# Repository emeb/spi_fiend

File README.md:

# spi_fiend
STM32F042-based USB to SPI device for programming iCE40 FPGAs

Most open-source projects that use Lattice iCE40 FPGAs rely on the FTDI
FT2232 High-speed UART/FIFO chip to provide a SPI interface for programming
the FPGA and SPI Flash chip which contains the bitstream for self-configuration
at power-up. I've got nothing against FTDI, but the chips are big, require
a crystal and are fairly expensive in DIY quantities. On top of that I've been
using STM32 for years and have been looking for an excuse to dig into some
more USB applications so a USB to SPI bridge seemed like a good place to start.

This device uses the small and inexpensive STM32F042F6P6 in a 20-pin TSSOP
package. It supports crystal-less USB operation by syncing its internal RC
oscillator to the USB SOF signal and has enough SRAM and Flash to support a
moderately complex feature set:

* USB powered
* Crystal-less operation
* Presents an ordinary ACM / CDC class device that looks like a serial port.
* Supports direct loading into the iCE40 SRAM for quick development cycles.
* Supports read/write/erase of standard SPI Flash devices used for FPGA configuration.
* Includes automatic swapping of MOSI/MISO when switching between FPGA and SPI Flash.
* MCU Serial port is pinned out for debugging and future expansion.

## prerequisites
To build this you will need the following tools:

* Kicad - schematic & PCB editor.
* GCC ARM Embedded - cross-compiler for ARM Cortex M: https://developer.arm.com/tools-and-software/open-source-software/developer-tools/gnu-toolchain/gnu-rm
* dfu-util - USB DFU driver application available in most distributions.
* Basic Linux user C compiler (for host application)

## Building Hardware

The board design is available in the 'hardware' directory. The Kicad PCB can
be submitted directly to OSHpark.com, or traditional Gerbers can be exported
using the application. Part values and packages are noted in the schematic.

Note: in the Revision 1 PCB layout the USB connector doesn't overhang the PCB
edge and there is a slight interference with the lower lip. Filing a slight
chamfer on the PCB edge under the connector will allow it to sit flush to the
board.

## Building Firmware

The [Firmware README](firmware/README.md) has instructions on building the
preferred firmware for the SPI Fiend.

## Building Host Application

The host appliction runs on a Linux PC and communicates with the hardware
device via standard USB Serial protocols. Build the host application by changing
to the 'host' directory and executing 'make'. The built-in help should provide
a guide to available options, but here's a quick list of common actions:

* load a binary into the FPGA: ./cdc_prog BINARY_FILE
* load a binary into SPI Flash: ./cdc_prog -a ADDRESS -w BINARY_FILE
* read SPI flash contents to a file: ./cdc_prog -a ADDRESS -l LENGTH -r > OUTPUT_FILE
* erase SPI FLASH block: ./cdc_prog -a ADDRESS -e
* read SPI Flash ID: ./cdc_prog -i

In ordinary operation, the LED nearest the USB connector lights to indicate powerup,
the center LED lights when an error is detected during operation and the outer LED
lights when programming SPI flash.

## Status
### 2019-05-06
Initial commit with hardware, firmware and host application

### 2022-11-11
Updated with dual firmware that supports FPGA, flash and UART

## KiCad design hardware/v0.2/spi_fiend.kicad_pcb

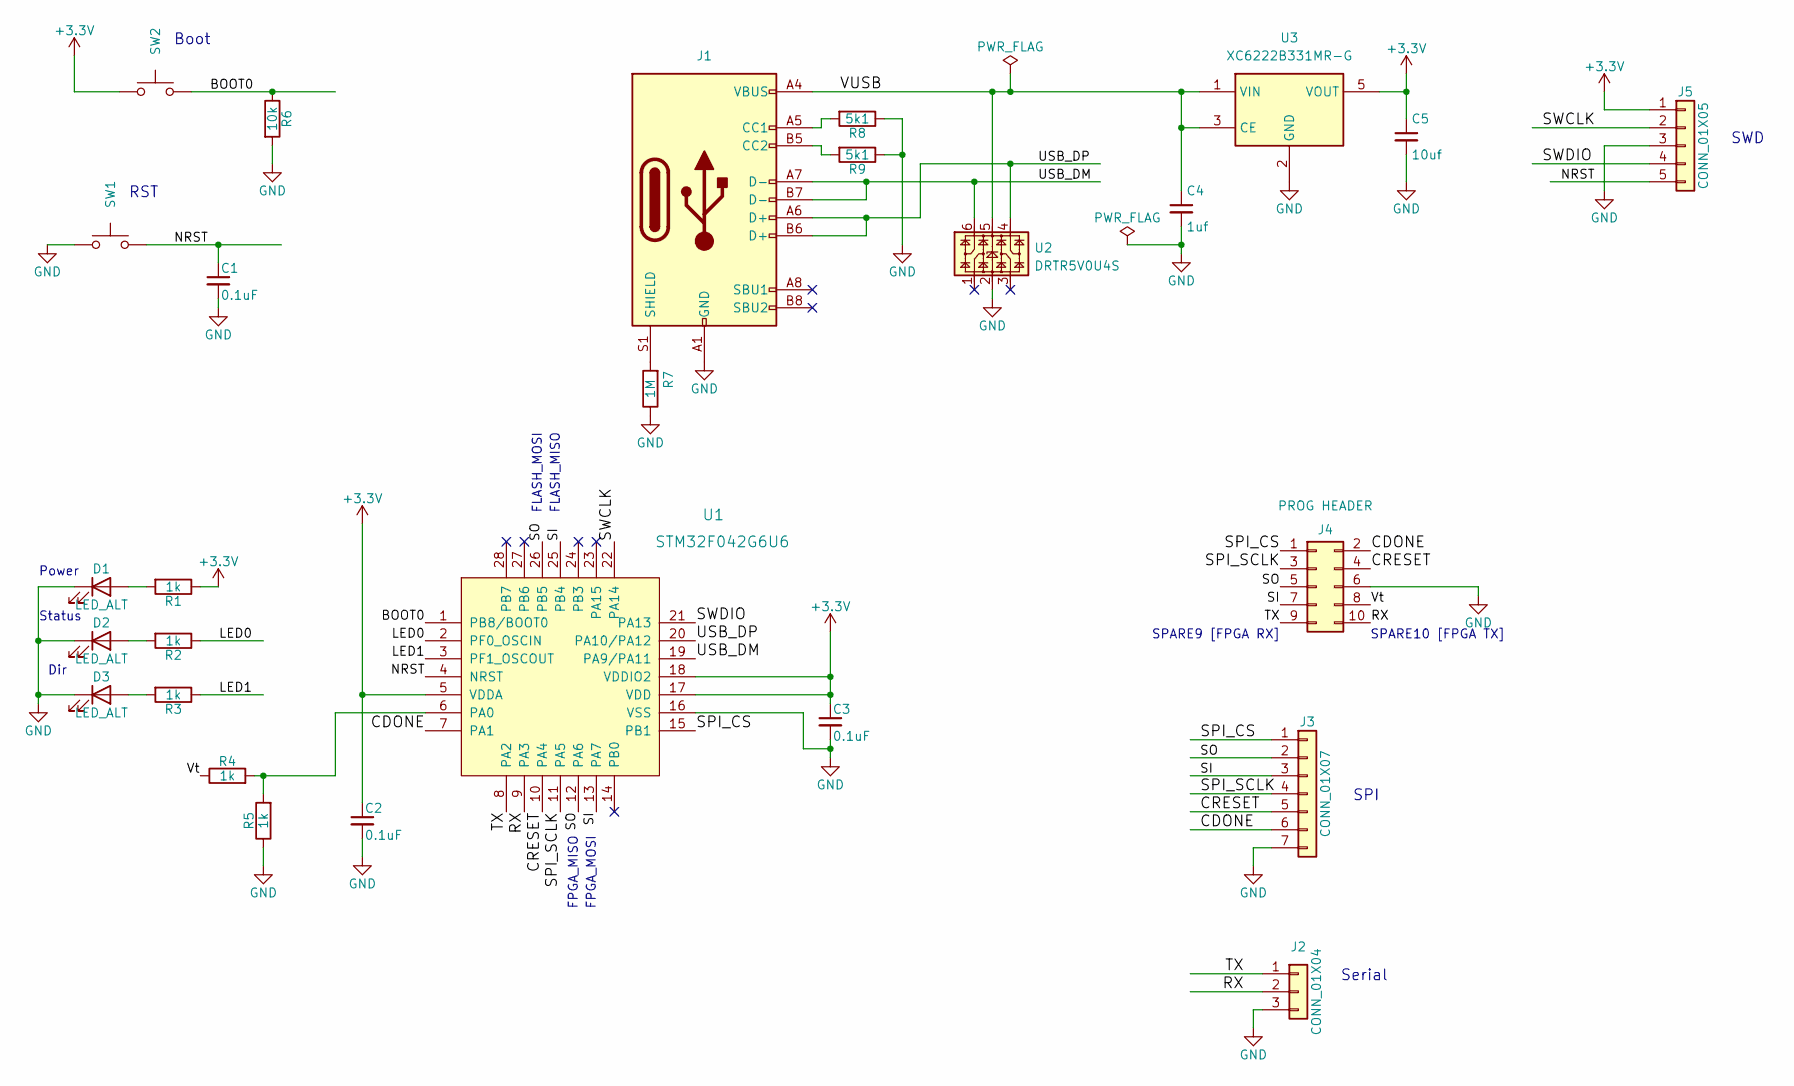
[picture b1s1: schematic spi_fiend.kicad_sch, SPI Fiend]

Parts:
C1, C2, C3: 0.1uF; C_0402_1005Metric
C4: 1uf; C_0402_1005Metric
C5: 10uf; C_0805_2012Metric
D1, D2, D3: LED_ALT; LED_0603_1608Metric
J1: USB_C_Receptacle_USB2.0; USB_C_Receptacle_HRO_TYPE-C-31-M-12
J2: CONN_01X04; PinHeader_1x03_P2.54mm_Vertical
J3: CONN_01X07; PinHeader_1x07_P2.54mm_Vertical
J4: PROG HEADER; PinHeader_2x05_P1.27mm_Vertical_SMD
J5: CONN_01X05; PinHeader_1x05_P2.54mm_Vertical
R1, R2, R3, R4, R5: 1k; R_0402_1005Metric
R6: 10k; R_0402_1005Metric
R7: 1M; R_0402_1005Metric
R8, R9: 5k1; R_0402_1005Metric
SW1, SW2: SW_Push; SW_SPST_PTS815
U1: STM32F042G6U6; IC_STM32F042G6U6
U2: DRTR5V0U4S; SOT-363_SC-70-6
U3: XC6222B331MR-G; SOT-23-5

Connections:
+3.3V: C2.1, C3.1, C5.1, J5.1, R1.1, SW2.1, U1.5 (VDDA), U1.17 (VDD), U1.18 (VDDIO2), U3.5 (VOUT)
/BOOT0: R6.1, SW2.2, U1.1 (PB8/BOOT0)
/CDONE: J3.6, J4.2, U1.7 (PA1)
/CRESET: J3.5, J4.4, U1.10 (PA4)
/LED0: R2.1, U1.2 (PF0_OSCIN)
/LED1: R3.1, U1.3 (PF1_OSCOUT)
/NRST: C1.1, J5.5, SW1.2, U1.4 (NRST)
/RX: J2.2, J4.10, U1.9 (PA3)
/SI: J3.3, J4.7, U1.13 (PA7), U1.25 (PB4)
/SO: J3.2, J4.5, U1.12 (PA6), U1.26 (PB5)
/SPI_CS: J3.1, J4.1, U1.15 (PB1)
/SPI_SCLK: J3.4, J4.3, U1.11 (PA5)
/SWCLK: J5.2, U1.22 (PA14)
/SWDIO: J5.4, U1.21 (PA13)
/TX: J2.1, J4.9, U1.8 (PA2)
/USB_DM: J1.A7 (D-), J1.B7 (D-), U1.19 (PA9/PA11), U2.6
/USB_DP: J1.A6 (D+), J1.B6 (D+), U1.20 (PA10/PA12), U2.4
/VUSB: C4.1, J1.A4 (VBUS), J1.A9 (VBUS), J1.B4 (VBUS), J1.B9 (VBUS), U2.5, U3.1 (VIN), U3.3 (CE)
/Vt: J4.8, R4.1
GND: C1.2, C2.2, C3.2, C4.2, C5.2, D1.1 (K), D2.1 (K), D3.1 (K), J1.A1 (GND), J1.A12 (GND), J1.B1 (GND), J1.B12 (GND), J2.3, J3.7, J4.6, J5.3, R5.1, R6.2, R7.1, R8.1, R9.1, SW1.1, U1.16 (VSS), U2.2, U3.2 (GND)
unnamed: D1.2 (A), R1.2
unnamed: D2.2 (A), R2.2
unnamed: D3.2 (A), R3.2
unnamed: J1.A5 (CC1), R8.2
unnamed: J1.B5 (CC2), R9.2
unnamed: J1.S1 (SHIELD), R7.2
unnamed: R4.2, R5.2, U1.6 (PA0)

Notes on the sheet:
FPGA_MISO
SWD
FPGA_MOSI
Serial
RST
Status
SPI
Power
Dir
FLASH_MOSI
Boot
SPARE9 [FPGA RX]
FLASH_MISO
SPARE10 [FPGA TX]

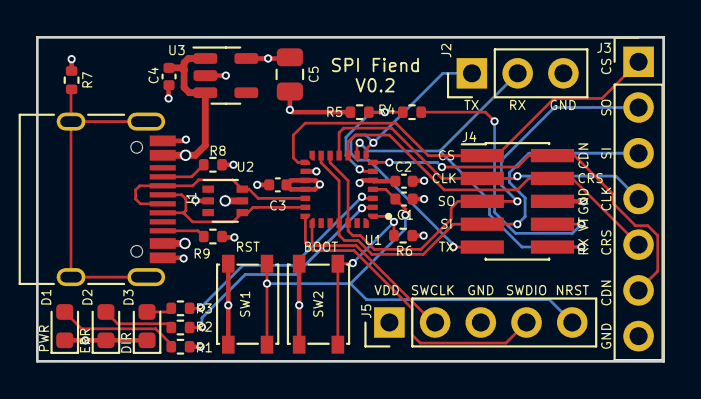
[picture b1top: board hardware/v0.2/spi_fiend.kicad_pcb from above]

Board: 4 copper layers, 34.8 x 18.0 mm, 28 parts (1 on the bottom side), 27 nets.

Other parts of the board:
Ref**: Val**; avatar_small

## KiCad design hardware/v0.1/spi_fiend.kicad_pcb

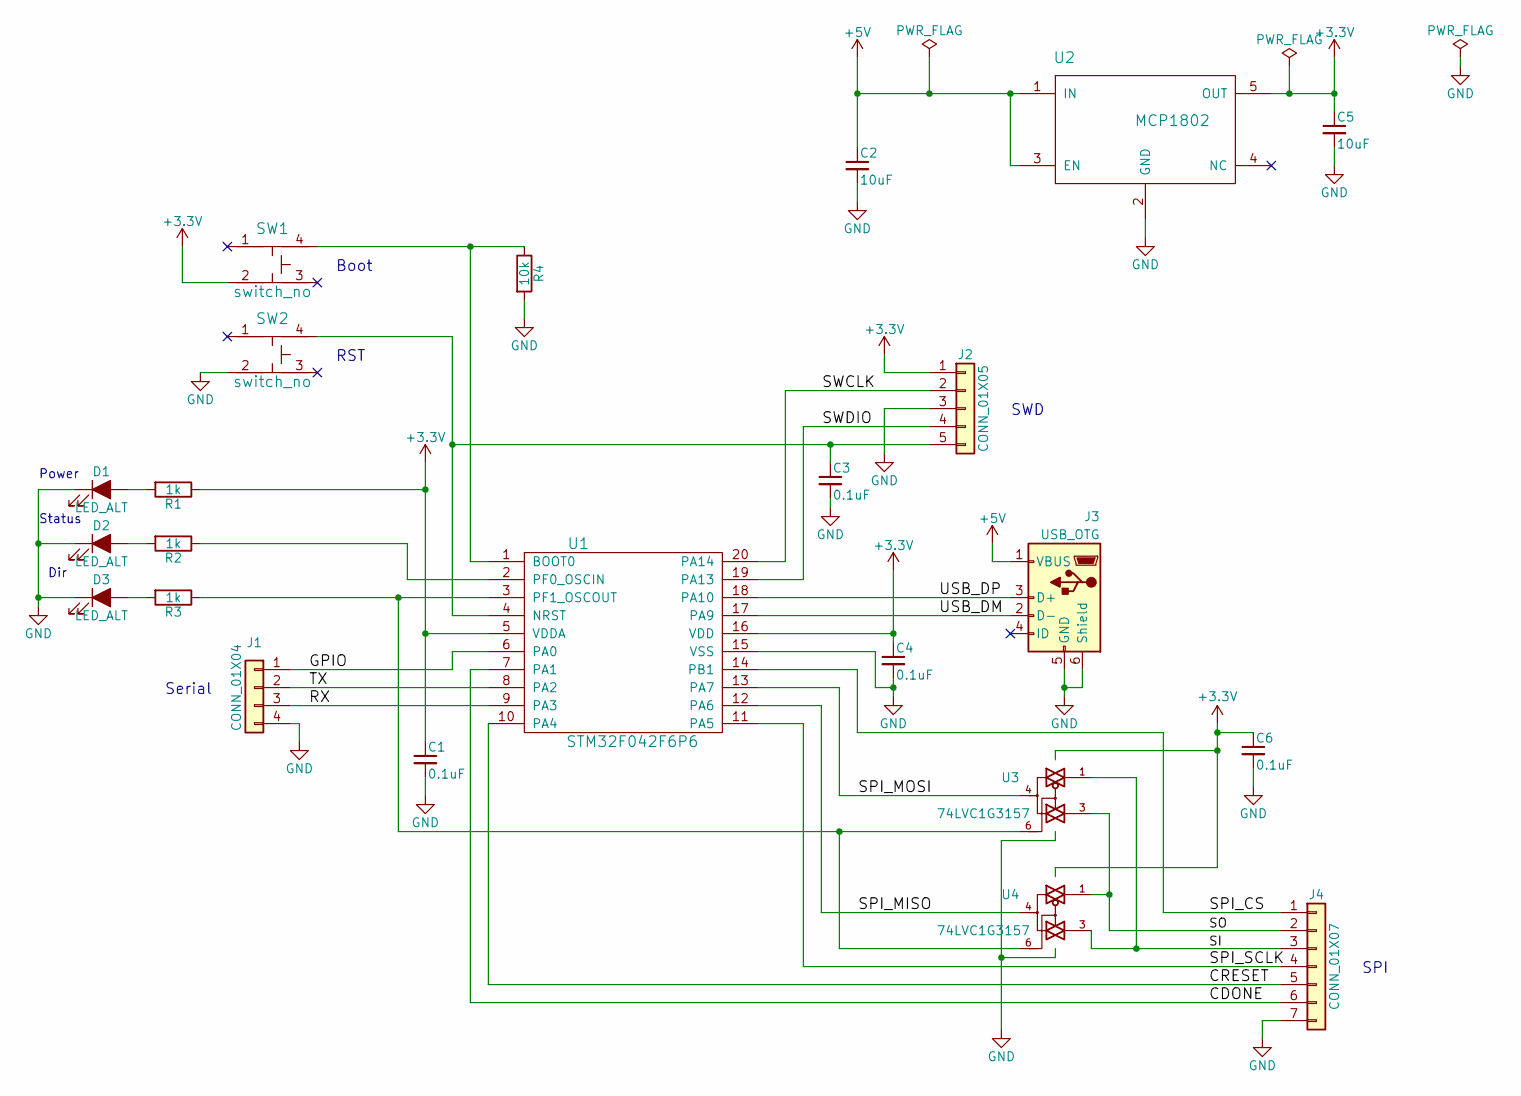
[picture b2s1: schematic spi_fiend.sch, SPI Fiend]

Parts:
C1, C3, C4, C6: 0.1uF; C_0603_HandSoldering
C2, C5: 10uF; C_0805_HandSoldering
D1, D2, D3: LED_ALT; LED_0603_HandSoldering
J1: CONN_01X04; Pin_Header_Straight_1x04_Pitch2.54mm
J2: CONN_01X05; Pin_Header_Straight_1x05_Pitch2.54mm
J3: USB_OTG; USB_Micro-B_10103594-0001LF_NoSlot
J4: CONN_01X07; Pin_Header_Straight_1x07_Pitch2.54mm
R1, R2, R3: 1k; R_0603_HandSoldering
R4: 10k; R_0603_HandSoldering
SW1, SW2: switch_no; PUSHBUTTON_SMD_KMR2
U1: STM32F042F6P6; TSSOP-20_4.4x6.5mm_Pitch0.65mm
U2: MCP1802; SOT-23-5_HandSoldering
U3, U4: 74LVC1G3157; SOT-363_SC-70-6_Handsoldering

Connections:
+3V3: C1.1, C4.1, C5.1, C6.1, J2.1, R1.1, SW1.2, U1.5 (VDDA), U1.16 (VDD), U2.5 (OUT), U3.5 (VCC), U4.5 (VCC)
+5V: C2.1, J3.1 (VBUS), U2.1 (IN), U2.3 (EN)
/CDONE: J4.6, U1.7 (PA1)
/CRESET: J4.5, U1.10 (PA4)
/GPIO: J1.1, U1.6 (PA0)
/RX: J1.3, U1.9 (PA3)
/SI: J4.3, U3.1, U4.3
/SO: J4.2, U3.3, U4.1
/SPI_CS: J4.1, U1.14 (PB1)
/SPI_MISO: U1.12 (PA6), U4.4
/SPI_MOSI: U1.13 (PA7), U3.4
/SPI_SCLK: J4.4, U1.11 (PA5)
/SWCLK: J2.2, U1.20 (PA14)
/SWDIO: J2.4, U1.19 (PA13)
/TX: J1.2, U1.8 (PA2)
/USB_DM: J3.2 (D-), U1.17 (PA9)
/USB_DP: J3.3 (D+), U1.18 (PA10)
GND: C1.2, C2.2, C3.2, C4.2, C5.2, C6.2, D1.1 (K), D2.1 (K), D3.1 (K), J1.4, J2.3, J3.5 (GND), J3.6 (Shield), J4.7, R4.2, SW2.2, U1.15 (VSS), U2.2 (GND), U3.2 (GND), U4.2 (GND)
unnamed: C3.1, J2.5, SW2.4, U1.4 (NRST)
unnamed: D1.2 (A), R1.2
unnamed: D2.2 (A), R2.2
unnamed: D3.2 (A), R3.2
unnamed: R2.1, U1.2 (PF0_OSCIN)
unnamed: R3.1, U1.3 (PF1_OSCOUT), U3.6, U4.6
unnamed: R4.1, SW1.4, U1.1 (BOOT0)

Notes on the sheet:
Boot
RST
Serial
SPI
SWD
Power
Status
Dir

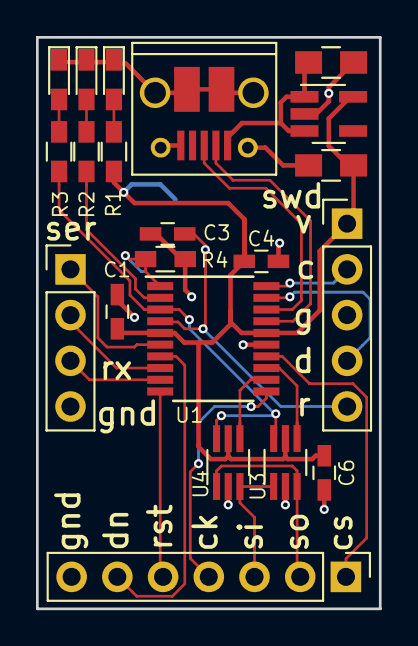
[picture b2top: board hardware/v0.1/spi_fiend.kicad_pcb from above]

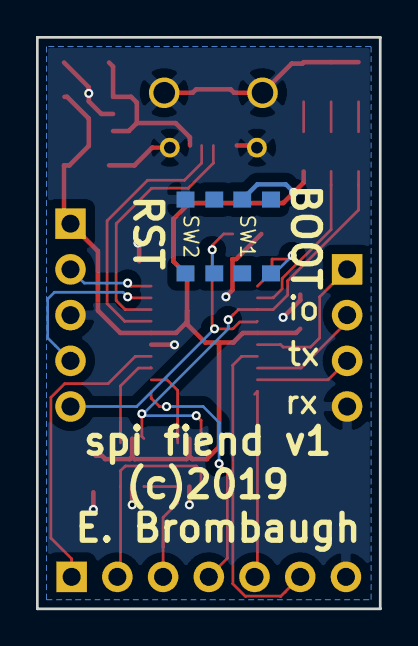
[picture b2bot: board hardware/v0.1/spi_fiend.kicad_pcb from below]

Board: 2 copper layers, 19.1 x 31.8 mm, 23 parts (2 on the bottom side), 25 nets.

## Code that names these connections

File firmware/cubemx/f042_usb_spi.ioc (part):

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Mcu.Name=STM32F042F6Px
Mcu.Package=TSSOP20
Mcu.UserName=STM32F042F6Px
PA0.GPIOParameters=GPIO_Label
PA0.GPIO_Label=GPIO0
PA0.Signal=GPIO_Output
PA1.GPIOParameters=GPIO_Label
PA1.GPIO_Label=CDONE
PA1.Signal=GPIO_Input
PA11.Mode=Device
PA11.Signal=USB_DM
PA12.Mode=Device
PA12.Signal=USB_DP
PA13.Mode=Serial_Wire
PA13.Signal=SYS_SWDIO
PA14.Mode=Serial_Wire
PA14.Signal=SYS_SWCLK
PA2.Mode=Asynchronous
PA2.Signal=USART2_TX
PA3.Mode=Asynchronous
PA3.Signal=USART2_RX
PA4.GPIOParameters=GPIO_Label
PA4.GPIO_Label=CRST
PA4.Signal=GPIO_Output
PA5.Mode=Full_Duplex_Master
PA5.Signal=SPI1_SCK
PA6.Mode=Full_Duplex_Master
PA6.Signal=SPI1_MISO
PA7.Mode=Full_Duplex_Master
PA7.Signal=SPI1_MOSI
PB1.GPIOParameters=GPIO_Label
PB1.GPIO_Label=SPI_CS
PB1.Signal=GPIO_Output
PB8.GPIOParameters=GPIO_Label
PB8.GPIO_Label=BOOT
PB8.Signal=GPIO_Output
PF0-OSC_IN.GPIOParameters=GPIO_Label
PF0-OSC_IN.GPIO_Label=Status
PF0-OSC_IN.Signal=GPIO_Output
PF1-OSC_OUT.GPIOParameters=GPIO_Label
PF1-OSC_OUT.GPIO_Label=DIR
PF1-OSC_OUT.Signal=GPIO_Output
RCC.SYSCLKFreq_VALUE=48000000
RCC.SYSCLKSource=RCC_SYSCLKSOURCE_HSI48
board=custom

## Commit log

2019-05-06 Add hardware, firmware, host and documentation
2022-11-11 Rearranged and added dual firmware based on TinyUSB
2022-11-11 Updated READMEs
2022-11-11 Remove redundant files
2022-11-17 Remove unused file
2022-11-17 move spi driver to common
2022-11-19 Clean up some uninit stuff, update IOC file for latest HW
2022-11-26 Updated with official PID code from pid.codes
2022-11-27 Started V0.2 hardware
2022-11-27 Start layout
2022-11-27 P&R almost done.
2022-11-27 Revert "P&R almost done."
    This reverts commit 97a49ac74aeb3e6297260b20c9d5898586bb1314.
2022-11-27 Correct bad revert and remove backups dir
2022-11-28 Done
2022-11-30 Fix 3D stuff

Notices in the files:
hardware/v0.1/spi_fiend.kicad_pcb:
(c)2019
hardware/v0.2/spi_fiend.kicad_pcb:
(c) 2022 E. Brombaugh
